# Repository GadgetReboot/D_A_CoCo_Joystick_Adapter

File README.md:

# D_A_CoCo_Joystick_Adapter
Tandy CoCo Joystick Adapter:  Digital to Analog Joystick Circuit
<br><br><br><br>
Use 5v/GND digital signals to control the analog joystick input of a Tandy Color Computer.<br>
When input buttons are not pressed, the joystick port sees approx. 5v / 2 = 2.5v, centering the joystick axis.
When a button is pressed, the joystick port sees 0V or 5V, representing the axis being at min or max of the analog range.

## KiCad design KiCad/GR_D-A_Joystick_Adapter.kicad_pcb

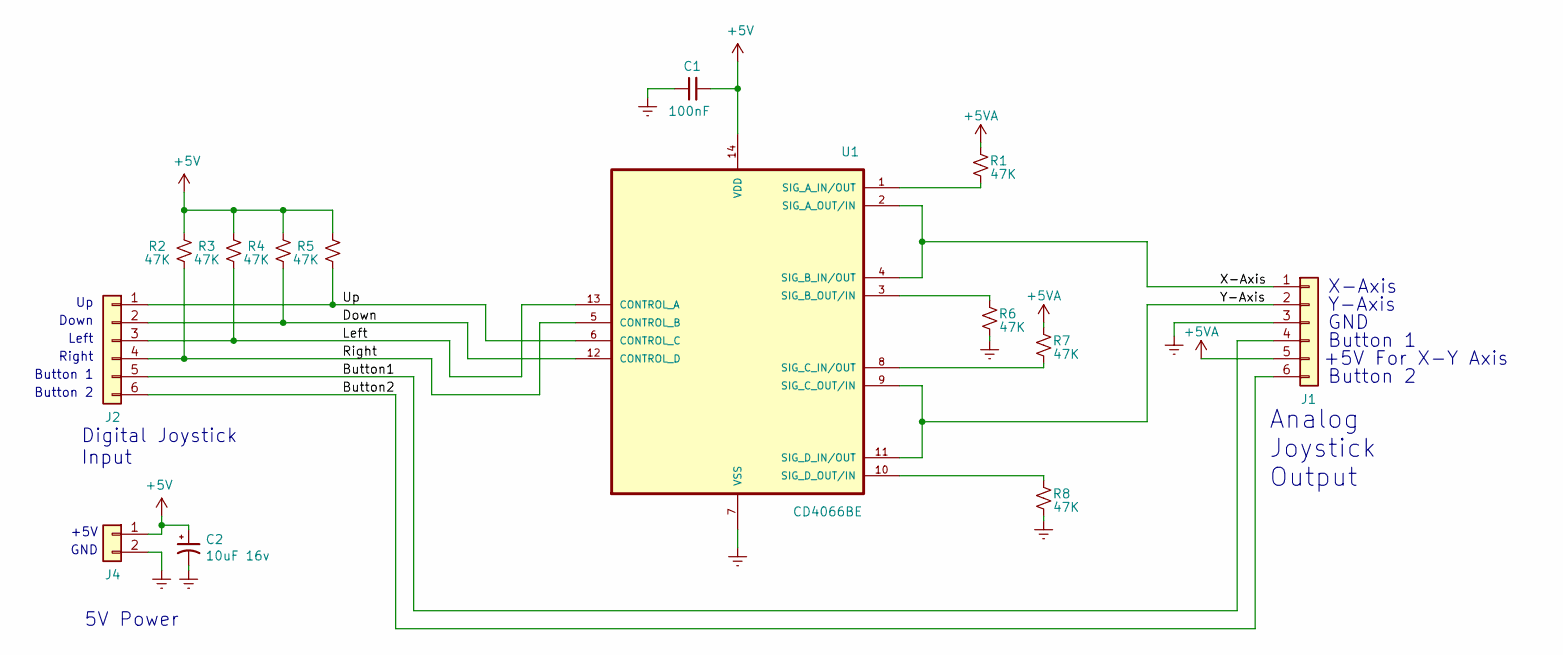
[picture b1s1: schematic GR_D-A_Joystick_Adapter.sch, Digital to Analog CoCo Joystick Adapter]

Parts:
C1: 100nF; C_Disc_D3.8mm_W2.6mm_P2.50mm
C2: 10uF 16v; CP_Radial_D5.0mm_P2.50mm
J1, J2: Conn_01x06; PinHeader_1x06_P2.54mm_Vertical
J4: Conn_01x02; PinHeader_1x02_P2.54mm_Vertical
R1, R2, R3, R4, R5, R6, R7, R8: 47K; R_Axial_DIN0309_L9.0mm_D3.2mm_P12.70mm_Horizontal
U1: CD4066BE; DIP-14_W7.62mm_Socket_LongPads

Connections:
+5V: C1.2, C2.1, J4.1, R2.1, R3.1, R4.1, R5.1, U1.14 (VDD)
+5VA: J1.5, R1.1, R7.1
/Button1: J1.4, J2.5
/Button2: J1.6, J2.6
/Down: J2.2, R4.2, U1.12 (CONTROL_D)
/Left: J2.3, R3.2, U1.13 (CONTROL_A)
/Right: J2.4, R2.2, U1.5 (CONTROL_B)
/Up: J2.1, R5.2, U1.6 (CONTROL_C)
/X-Axis: J1.1, U1.2 (SIG_A_OUT/IN), U1.4 (SIG_B_IN/OUT)
/Y-Axis: J1.2, U1.9 (SIG_C_OUT/IN), U1.11 (SIG_D_IN/OUT)
GNDREF: C1.1, C2.2, J1.3, J4.2, R6.2, R8.2, U1.7 (VSS)
unnamed: R1.2, U1.1 (SIG_A_IN/OUT)
unnamed: R6.1, U1.3 (SIG_B_OUT/IN)
unnamed: R7.2, U1.8 (SIG_C_IN/OUT)
unnamed: R8.1, U1.10 (SIG_D_OUT/IN)

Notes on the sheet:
5V Power
+5V
GND
Analog Joystick Output
X-Axis
Y-Axis
Button 1
+5V For X-Y Axis
Button 2
Digital Joystick Input
Button 2
Right
Left
Down

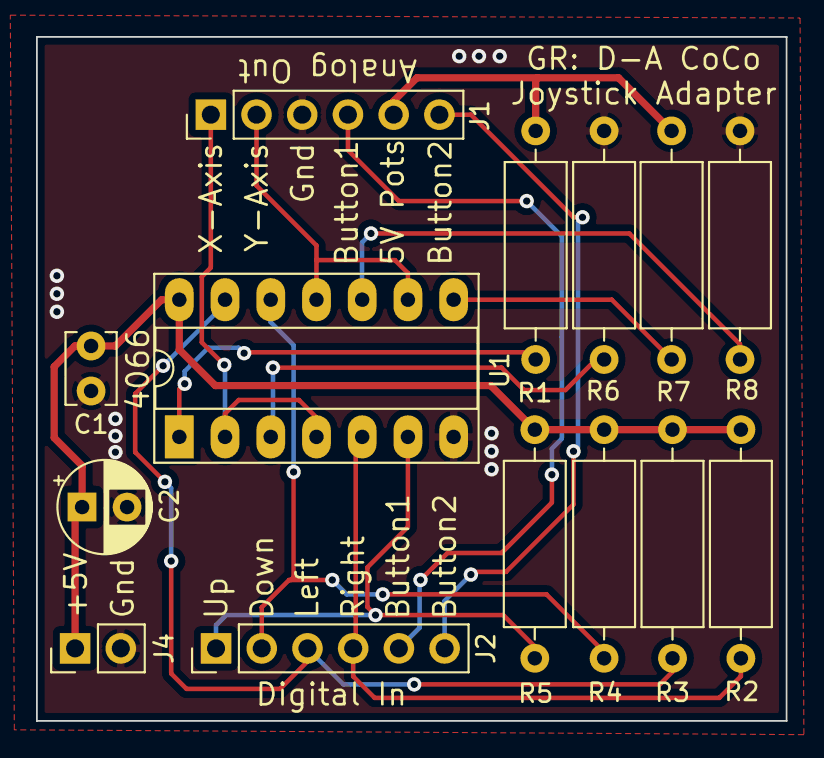
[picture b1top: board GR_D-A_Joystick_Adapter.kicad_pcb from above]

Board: 2 copper layers, 41.7 x 38.0 mm, 14 parts (0 on the bottom side), 15 nets.
